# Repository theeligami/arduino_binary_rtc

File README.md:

## A binary real-time-clock using an Arduino Uno and a RTC_DS3231

This clock will display the time on some LEDs in binary format.
For the best results, please make sure to follow the layout plan and the schematic.

__This is a work in progress! I am not responsible for any damages to you or your property if you attempt to build this project yourself!__

____

### Requirements:
For the code to work you will need adafruit's [RTClib](https://github.com/adafruit/RTClib). Just follow their instructions to install it and you're good to go.

___

### Note:
I am also working on a wall-mount version of the clock as well as a custom pcb. Instead of a DS3231 a DCF-77 time signal receiver will be used by the new circuit.
The project will also be ported to pure C instead of Arduino C++ in the future. For more information check out the "kicad" directory.

___

### Known Issues:
__The time displayed on the clock is off or from the wrong time zone:__

This is due to the \__DATE__ variable (which is used by the DS3231) in your system being wrong. Check if your UEFI/BIOS time is set correctly.
You can set you timezone with the help of the TIMEZONE macro. TIMEZONE will be added to the hours variable.

_Feel free to report errors and bugs or give input on possible optimizations!_

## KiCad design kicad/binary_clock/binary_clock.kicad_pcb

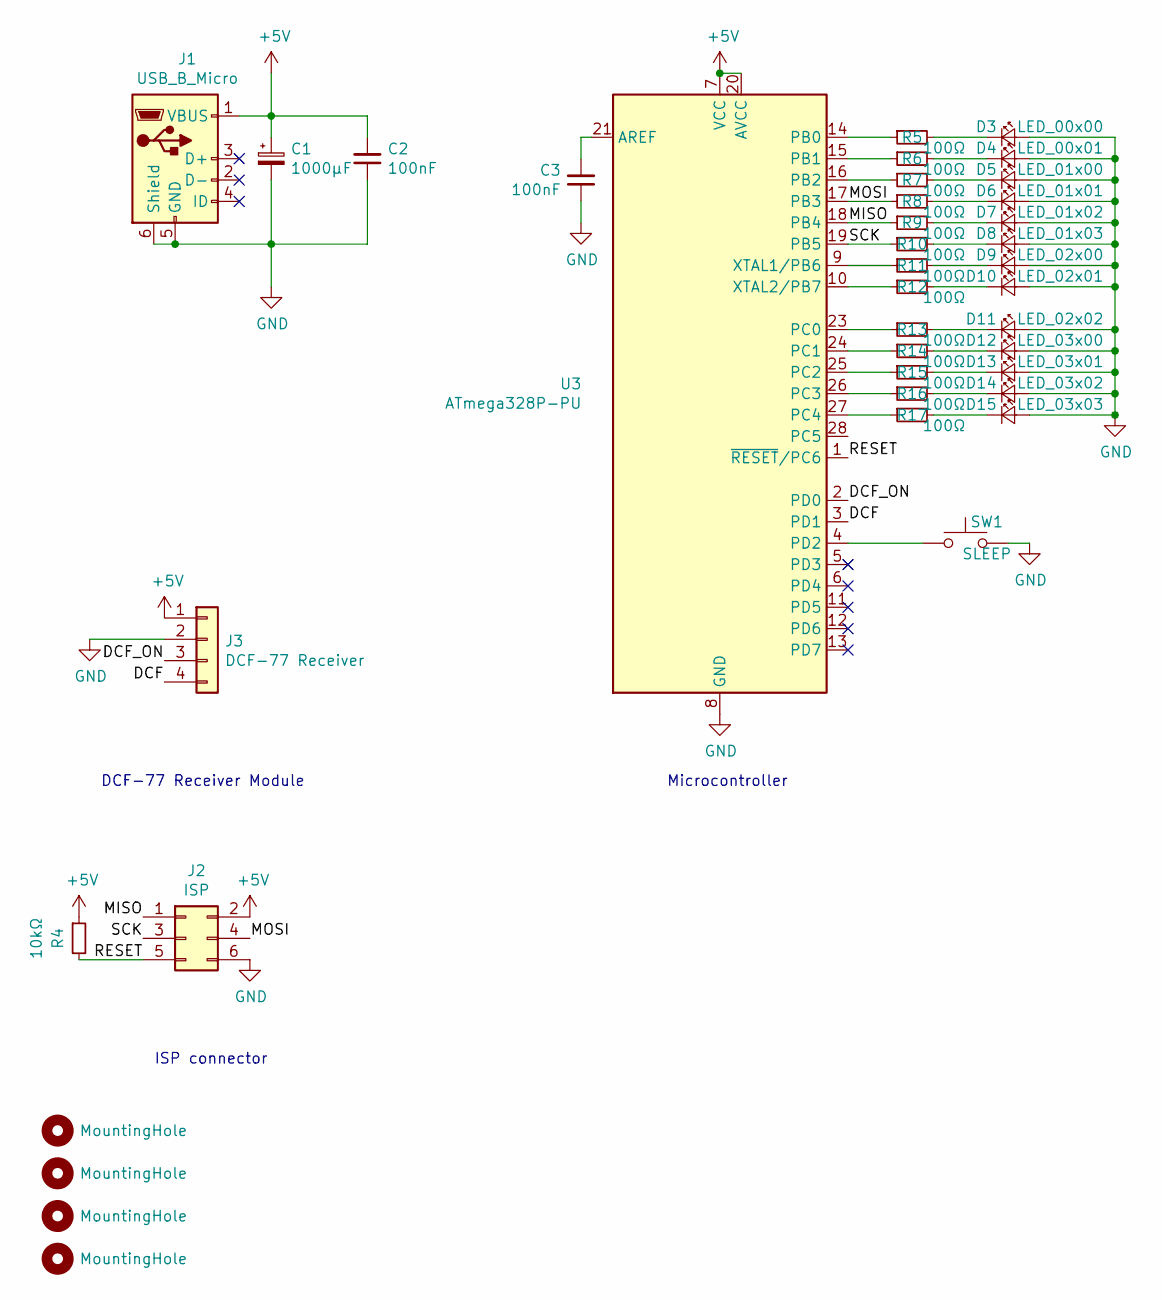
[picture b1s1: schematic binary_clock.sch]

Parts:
C1: 1000µF; CP_Elec_10x10
C2, C3: 100nF; C_0805_2012Metric_Pad1.15x1.40mm_HandSolder
D3: LED_00x00; LED_D5.0mm
D4: LED_00x01; LED_D5.0mm
D5: LED_01x00; LED_D5.0mm
D6: LED_01x01; LED_D5.0mm
D7: LED_01x02; LED_D5.0mm
D8: LED_01x03; LED_D5.0mm
D9: LED_02x00; LED_D5.0mm
D10: LED_02x01; LED_D5.0mm
D11: LED_02x02; LED_D5.0mm
D12: LED_03x00; LED_D5.0mm
D13: LED_03x01; LED_D5.0mm
D14: LED_03x02; LED_D5.0mm
D15: LED_03x03; LED_D5.0mm
H1, H2, H3, H4: MountingHole; MountingHole_3.2mm_M3
J1: USB_B_Micro; USB_Mini-B_Lumberg_2486_01_Horizontal
J2: ISP; PinHeader_2x03_P2.00mm_Vertical
J3: DCF-77 Receiver; PinSocket_1x04_P2.00mm_Vertical
R4: 10kΩ; R_0805_2012Metric
R5, R6, R7, R8, R9, R10, R11, R12, R13, R14, R15, R16, R17: 100Ω; R_0805_2012Metric
SW1: SLEEP; SW_PUSH_6mm
U3: ATmega328P-PU; DIP-28_W7.62mm

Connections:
+5V: C1.1, C2.2, J1.1 (VBUS), J2.2, J3.1, R4.1, U3.7 (VCC), U3.20 (AVCC)
/DCF: J3.4, U3.3 (PD1)
/DCF_ON: J3.3, U3.2 (PD0)
/MISO: J2.1, R9.1, U3.18 (PB4)
/MOSI: J2.4, R8.1, U3.17 (PB3)
/RESET: J2.5, R4.2, U3.1 (~RESET~/PC6)
/SCK: J2.3, R10.1, U3.19 (PB5)
GND: C1.2, C2.1, C3.1, D3.2 (A), D4.2 (A), D5.2 (A), D6.2 (A), D7.2 (A), D8.2 (A), D9.2 (A), D10.2 (A), D11.2 (A), D12.2 (A), D13.2 (A), D14.2 (A), D15.2 (A), J1.5 (GND), J1.6 (Shield), J2.6, J3.2, SW1.2, U3.8 (GND), U3.22 (GND)
unnamed: C3.2, U3.21 (AREF)
unnamed: D3.1 (K), R5.2
unnamed: D4.1 (K), R6.2
unnamed: D5.1 (K), R7.2
unnamed: D6.1 (K), R8.2
unnamed: D7.1 (K), R9.2
unnamed: D8.1 (K), R10.2
unnamed: D9.1 (K), R11.2
unnamed: D10.1 (K), R12.2
unnamed: D11.1 (K), R13.2
unnamed: D12.1 (K), R14.2
unnamed: D13.1 (K), R15.2
unnamed: D14.1 (K), R16.2
unnamed: D15.1 (K), R17.2
unnamed: R5.1, U3.14 (PB0)
unnamed: R6.1, U3.15 (PB1)
unnamed: R7.1, U3.16 (PB2)
unnamed: R11.1, U3.9 (XTAL1/PB6)
unnamed: R12.1, U3.10 (XTAL2/PB7)
unnamed: R13.1, U3.23 (PC0)
unnamed: R14.1, U3.24 (PC1)
unnamed: R15.1, U3.25 (PC2)
unnamed: R16.1, U3.26 (PC3)
unnamed: R17.1, U3.27 (PC4)
unnamed: SW1.1, U3.4 (PD2)

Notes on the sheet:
Microcontroller
ISP connector
DCF-77 Receiver Module

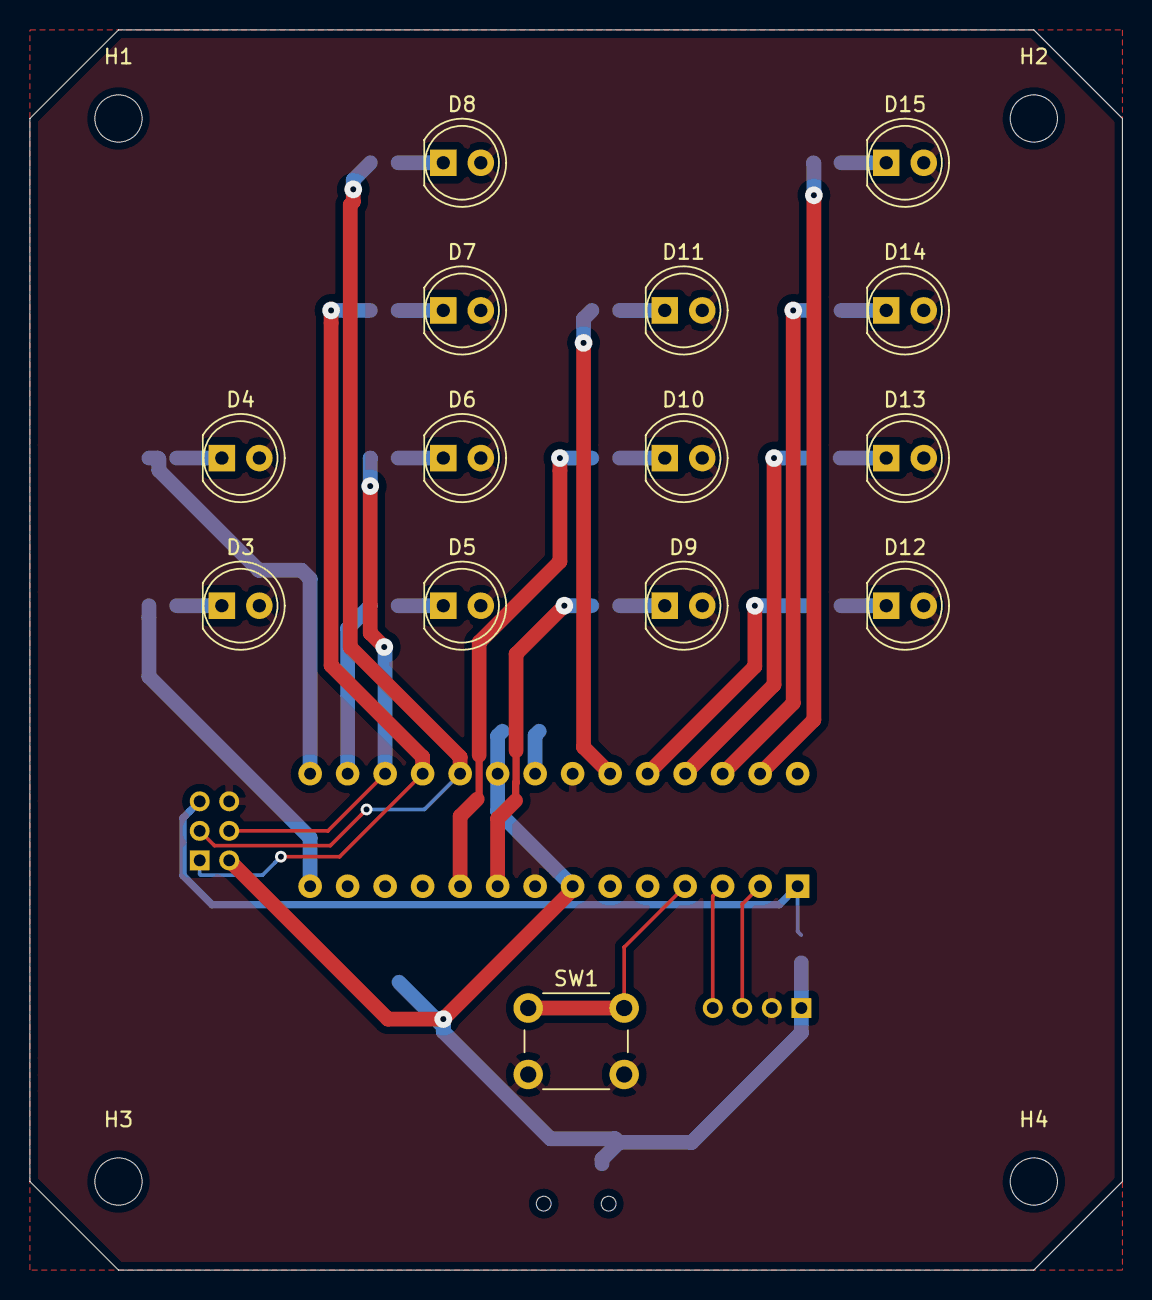
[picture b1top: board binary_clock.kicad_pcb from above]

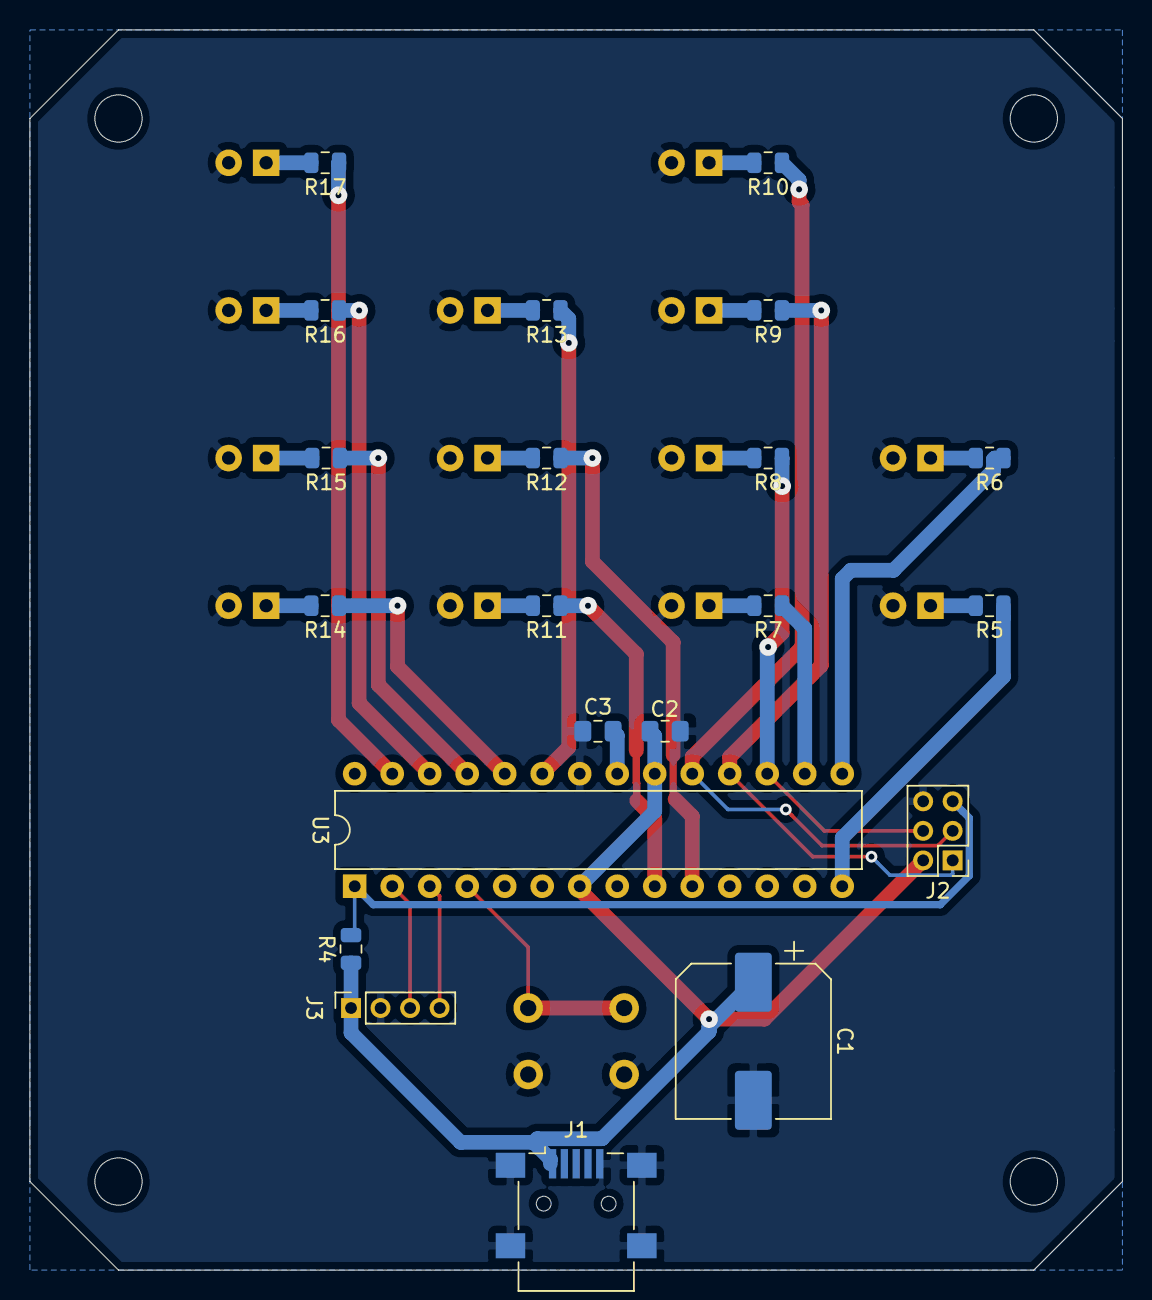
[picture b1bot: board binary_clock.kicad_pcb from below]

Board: 2 copper layers, 74.0 x 84.0 mm, 39 parts (21 on the bottom side), 33 nets.

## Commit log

2019-03-18 Working binary clock
2019-03-18 Create LICENSE
2019-03-18 Add a license header
2019-03-18 Edited names of LEDXX macros to DXX
2019-03-18 Added schematic
2019-03-18 Layout for LED setup
2019-03-18 New LED-Layout, changed format
2019-03-21 This is a test please ignore.
2019-03-21 Test
2019-09-01 Added timezone support for RTC
2019-09-01 Reorganized files. Added stl files for case.
2019-09-01 Removed old files.
2019-09-01 Added information about the TIMEZONE macro.
2019-09-02 Designed PCB and schematic for a custom board to fit into the wall mount version of the case.
2019-09-02 Removed old libs.
2019-09-02 Added info about project direction.
2019-09-02 Added Quarz Oscillator.
2020-07-01 Fuck this shit
